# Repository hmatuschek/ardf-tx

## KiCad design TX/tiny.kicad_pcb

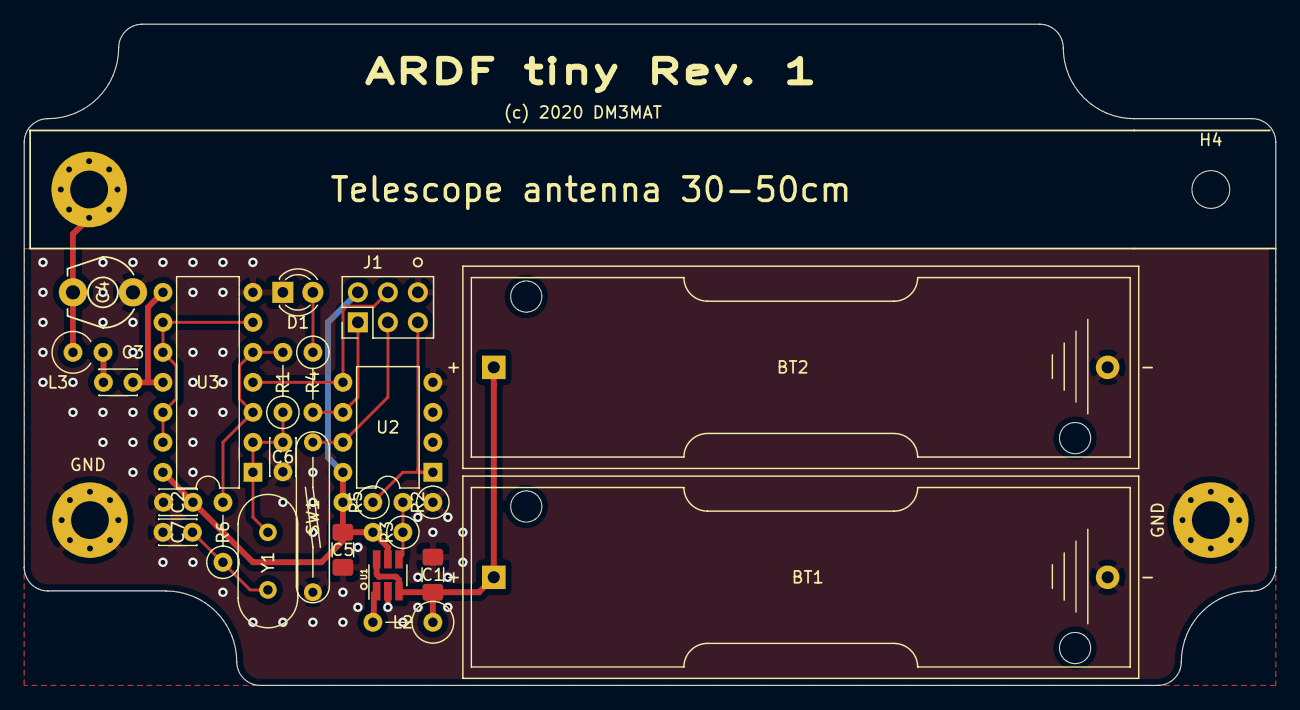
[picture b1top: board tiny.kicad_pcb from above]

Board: 2 copper layers, 106.0 x 56.0 mm, 28 parts (0 on the bottom side), 17 nets.

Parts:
BT1, BT2: 1.2V; BatteryHolder_Keystone_2460_1xAA
C1: 4.7u; C_1206_3216Metric_Pad1.42x1.75mm_HandSolder
C2, C3: 100n; C_Disc_D3.0mm_W2.0mm_P2.50mm
C4: 10p; C_Trimmer_TSC6_P5.00mm
C5: 10u; C_1206_3216Metric_Pad1.42x1.75mm_HandSolder
C6, C7: 33p; C_Disc_D3.0mm_W2.0mm_P2.50mm
D1: LED; LED_D3.0mm
H1: ANT; MountingHole_3.2mm_M3_Pad_Via
H2, H3: GND; MountingHole_3.2mm_M3_Pad_Via
H4: MountingHole; MountingHole_3.2mm_M3
J1: AVR-ISP-6; PinHeader_2x03_P2.54mm_Vertical
L2: 4.7u; L_Axial_L7.0mm_D3.3mm_P5.08mm_Vertical_Fastron_MICC
L3: 100u; L_Axial_L7.0mm_D3.3mm_P2.54mm_Vertical_Fastron_MICC
R1: 2.2M; R_Axial_DIN0207_L6.3mm_D2.5mm_P5.08mm_Vertical
R2: 562k; R_Axial_DIN0207_L6.3mm_D2.5mm_P2.54mm_Vertical
R3: 967k; R_Axial_DIN0207_L6.3mm_D2.5mm_P2.54mm_Vertical
R4: 650; R_Axial_DIN0207_L6.3mm_D2.5mm_P5.08mm_Vertical
R5: 10k; R_Axial_DIN0207_L6.3mm_D2.5mm_P2.54mm_Vertical
R6: 1.5k; R_Axial_DIN0207_L6.3mm_D2.5mm_P5.08mm_Vertical
SW1: Start/Stop; SW_Reed_Meder_MK6-5_P12.7
U1: MCP1640BCH; SOT-23-6_Handsoldering
U2: ATtiny45-20PU; DIP-8_W7.62mm
U3: 74HC00; DIP-14_W7.62mm
Y1: 3.579545; Crystal_HC49-U_Vertical

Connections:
+3V3: C2.2, C5.2, J1.2, R3.2, R5.2, U1.5, U2.8, U3.14
BTN: J1.3, SW1.1, U2.7
GND: BT1.2, BT2.2, C1.1, C2.1, C4.2, C5.1, C6.1, C7.1, D1.1, H2.1, H3.1, J1.6, R2.1, SW1.2, U1.2, U2.4, U3.7
KEY: J1.4, U2.5, U3.4
LED: J1.1, R4.2, U2.6
unnamed: BT1.1, BT2.1, C1.2, L2.1, U1.3, U1.6
unnamed: C3.1, U3.8, U3.11
unnamed: C3.2, L3.2
unnamed: C4.1, H1.1, L3.1
unnamed: C6.2, R1.1, U3.1, U3.2, Y1.1
unnamed: C7.2, R6.1, Y1.2
unnamed: D1.2, R4.1
unnamed: L2.2, U1.1
unnamed: R1.2, R6.2, U3.3, U3.5
unnamed: R2.2, R3.1, U1.4
unnamed: U3.6, U3.9, U3.10, U3.12, U3.13
RST: J1.5, R5.1, U2.1

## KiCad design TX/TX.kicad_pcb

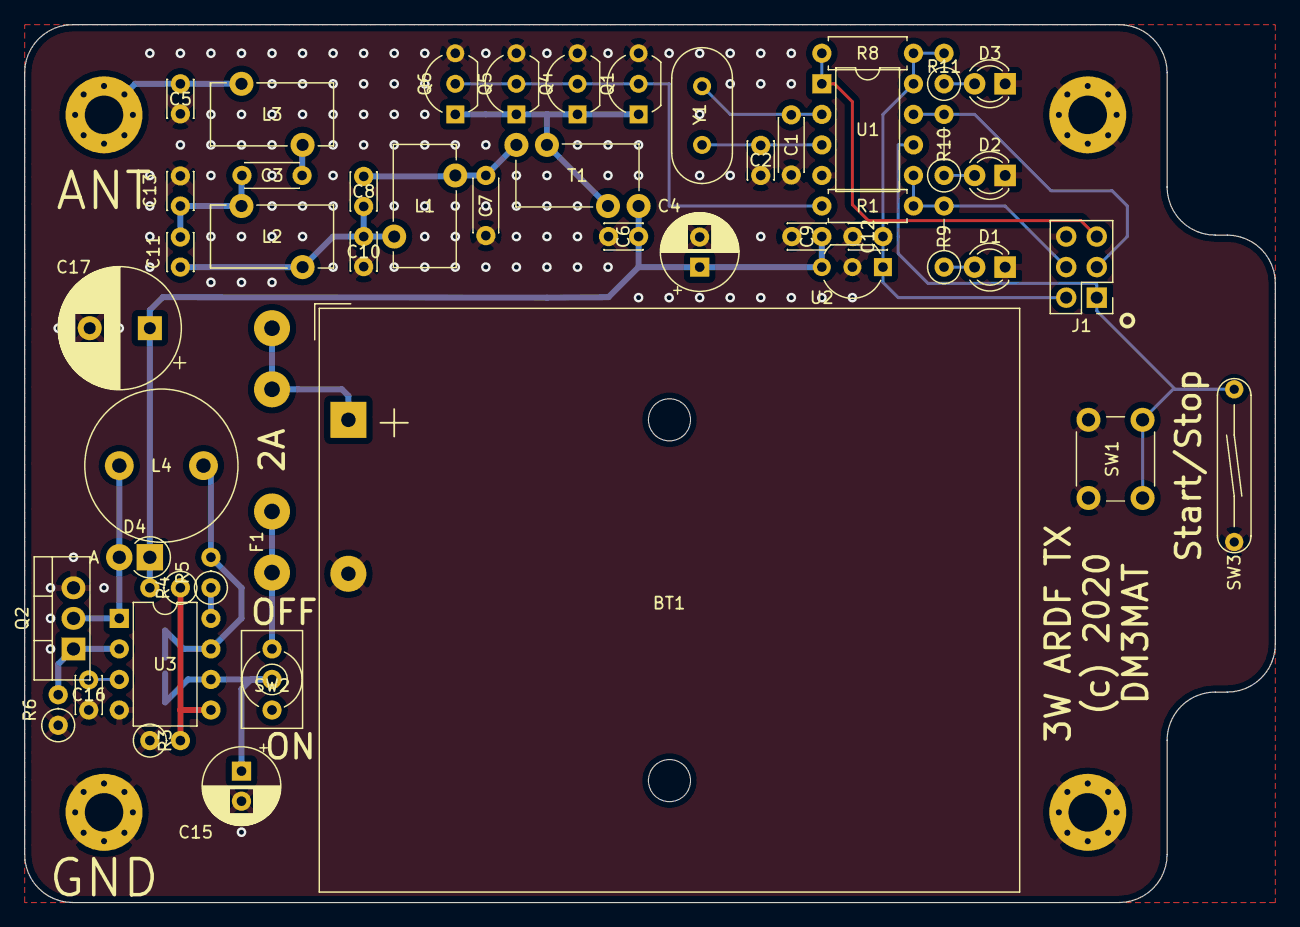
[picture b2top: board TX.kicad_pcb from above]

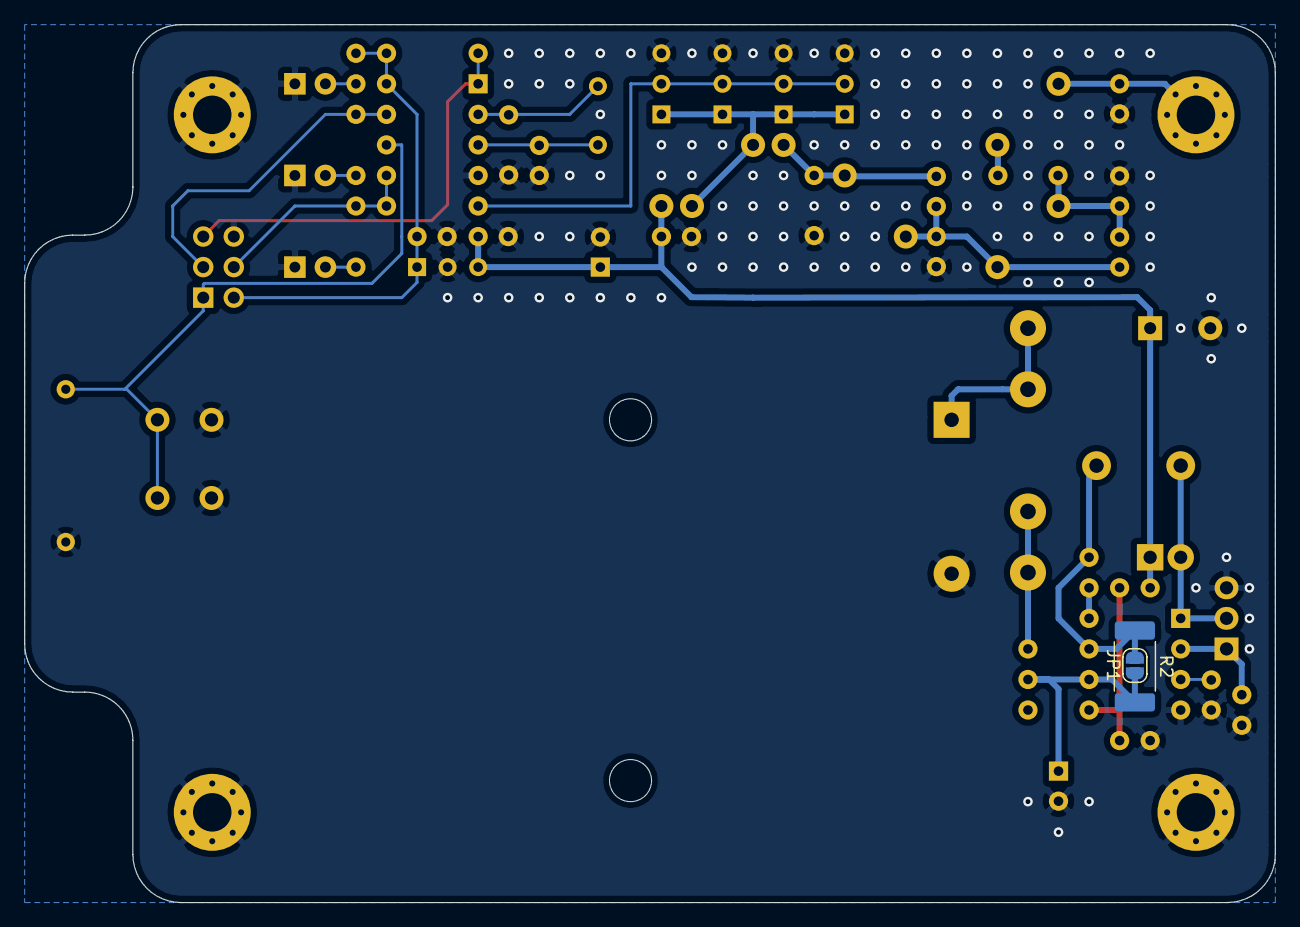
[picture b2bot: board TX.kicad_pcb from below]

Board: 2 copper layers, 104.0 x 73.0 mm, 55 parts (2 on the bottom side), 28 nets.

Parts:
BT1: 3.6V; BatteryHolder_TruPower_BH-331P_3xAA
C1: 22p; C_Disc_D4.3mm_W1.9mm_P5.00mm
C2: 22p; C_Disc_D3.0mm_W2.0mm_P2.50mm
C3: 220n; C_Disc_D4.3mm_W1.9mm_P5.00mm
C4: 100u; CP_Radial_D6.3mm_P2.50mm
C5: 47p; C_Disc_D3.0mm_W2.0mm_P2.50mm
C6, C9, C12: 100n; C_Disc_D3.0mm_W2.0mm_P2.50mm
C7: 820p; C_Disc_D4.3mm_W1.9mm_P5.00mm
C8: 150p; C_Disc_D3.0mm_W2.0mm_P2.50mm
C10: 1.2n; C_Disc_D3.0mm_W2.0mm_P2.50mm
C11: 390p; C_Disc_D3.0mm_W2.0mm_P2.50mm
C13: 560p; C_Disc_D3.0mm_W2.0mm_P2.50mm
C15: 220u; CP_Radial_D6.3mm_P2.50mm
C16: 470p; C_Disc_D3.0mm_W2.0mm_P2.50mm
C17: 470u; CP_Radial_D10.0mm_P5.00mm
D1, D2, D3: LED; LED_D3.0mm
D4: 1N5819; D_DO-41_SOD81_P2.54mm_Vertical_AnodeUp
F1: 2A Träge; Fuseholder_Cylinder-5x20mm_ESKA_Clip_Horizontal_Open
H1, H2, H3: GND; MountingHole_3.2mm_M3_Pad_Via
H4: ANT; MountingHole_3.2mm_M3_Pad_Via
J1: AVR-ISP-6; PinHeader_2x03_P2.54mm_Vertical
JP1: SolderJumper_2_Open; SolderJumper-2_P1.3mm_Open_RoundedPad1.0x1.5mm
L1: 2.2u; L_Toroid_Vertical_L10.0mm_W5.0mm_P5.08mm_Diagonal
L2: 1.8u; L_Toroid_Vertical_L10.0mm_W5.0mm_P5.08mm_Diagonal
L3: 42u; L_Toroid_Vertical_L10.0mm_W5.0mm_P5.08mm_Diagonal
L4: 20uH; L_Radial_D12.5mm_P7.00mm_Fastron_09HCP
Q1, Q4, Q5, Q6: BS170; TO-92_Inline_Wide
Q2: TIP41; TO-220-3_Vertical
R1: 100; R_Axial_DIN0207_L6.3mm_D2.5mm_P7.62mm_Horizontal
R2: 0.2; R_2512_6332Metric_Pad1.52x3.35mm_HandSolder
R3: 1k; R_Axial_DIN0207_L6.3mm_D2.5mm_P2.54mm_Vertical
R4: 6.2k; R_Axial_DIN0207_L6.3mm_D2.5mm_P2.54mm_Vertical
R5: 180; R_Axial_DIN0207_L6.3mm_D2.5mm_P2.54mm_Vertical
R6: 22; R_Axial_DIN0207_L6.3mm_D2.5mm_P2.54mm_Vertical
R8: 10k; R_Axial_DIN0207_L6.3mm_D2.5mm_P7.62mm_Horizontal
R9, R10: 1.5k; R_Axial_DIN0207_L6.3mm_D2.5mm_P5.08mm_Vertical
R11: 1.5k; R_Axial_DIN0207_L6.3mm_D2.5mm_P2.54mm_Vertical
SW1: Start/Stop; SW_PUSH_6mm_H7.3mm
SW2: ON; SW_Lever_RND-210-004371
SW3: EXT; SW_Reed_Meder_MK6-5_P12.7
T1: 2 x 10 @ FT37-43; Transformer_1P_1S_Toroid_Vertical_D10.5mm_Amidon-T37
U1: ATtiny45-20PU; DIP-8_W7.62mm
U2: L78L05; TO-92_Inline_Wide
U3: MC34063AP; DIP-8_W7.62mm
Y1: 14.31818MHz; Crystal_HC49-U_Vertical

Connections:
+5V: C12.1, J1.2, R8.2, R11.2, U1.8, U2.1
GND: BT1.2, C1.2, C2.2, C4.2, C5.2, C6.1, C7.2, C9.1, C10.2, C12.2, C13.2, C15.2, C16.2, C17.2, D1.1, D2.1, D3.1, H1.1, H2.1, H3.1, J1.6, Q1.3, Q2.3, Q4.3, Q5.3, Q6.3, R3.1, R6.1, SW1.2, SW3.2, U1.4, U2.2, U3.4
KEY: J1.4, R1.2, R9.2, U1.5
LED: J1.3, R10.2, U1.7
unnamed: BT1.1, F1.2
unnamed: C3.2, L3.1
unnamed: C5.1, H4.1, L3.2
unnamed: C7.1, C8.1, L1.1, T1.3
unnamed: C8.2, C10.1, C11.1, L1.2, L2.1
unnamed: C3.1, C11.2, C13.1, L2.2
unnamed: C15.1, JP1.1, R2.2, SW2.2, U3.6
unnamed: C16.1, U3.3
unnamed: D1.2, R9.1
unnamed: D2.2, R10.1
unnamed: D3.2, R11.1
unnamed: D4.2, L4.2, Q2.2, U3.1
unnamed: F1.1, SW2.1
unnamed: JP1.2, L4.1, R2.1, R5.2, U3.7
unnamed: Q1.1, Q4.1, Q5.1, Q6.1, T1.2, T1.4
unnamed: Q1.2, Q4.2, Q5.2, Q6.2, R1.1
unnamed: Q2.1, R6.2, U3.2
unnamed: R3.2, R4.1, U3.5
unnamed: R5.1, U3.8
RST: J1.5, R8.1, U1.1
SS: J1.1, SW1.1, SW3.1, U1.6
VCC: C4.1, C6.2, C9.2, C17.1, D4.1, R4.2, T1.1, U2.3
Xi: C1.1, U1.2, Y1.1
Xo: C2.1, U1.3, Y1.2

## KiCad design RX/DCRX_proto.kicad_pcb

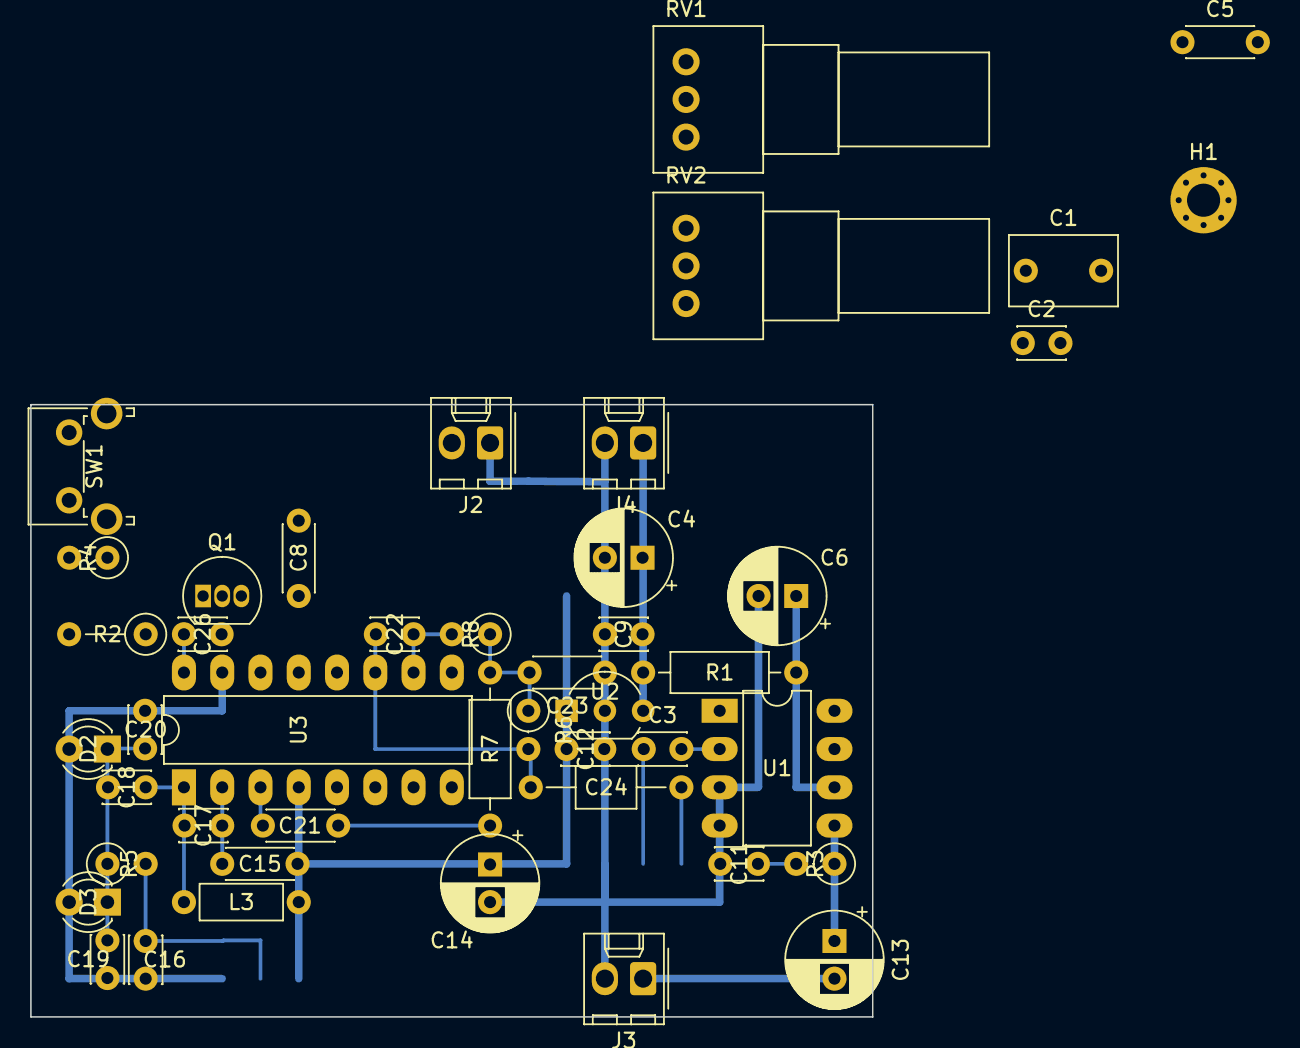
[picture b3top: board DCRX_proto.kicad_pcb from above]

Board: 2 copper layers, 55.9 x 40.6 mm, 45 parts (0 on the bottom side), 24 nets.

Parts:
C1: 30p; C_Rect_L7.0mm_W4.5mm_P5.00mm
C2: 220p; C_Disc_D3.0mm_W2.0mm_P2.50mm
C3, C9, C11, C12, C16, C18: 100n; C_Disc_D3.0mm_W2.0mm_P2.50mm
C4, C13: 100u; CP_Radial_D6.3mm_P2.50mm
C5, C8, C21: 100n; C_Disc_D4.3mm_W1.9mm_P5.00mm
C6, C14: 10u; CP_Radial_D6.3mm_P2.50mm
C15: 100p; C_Disc_D4.3mm_W1.9mm_P5.00mm
C17, C19: 100p; C_Disc_D3.0mm_W2.0mm_P2.50mm
C20: *; C_Disc_D3.0mm_W2.0mm_P2.50mm
C22: 2.2n; C_Disc_D3.0mm_W2.0mm_P2.50mm
C23: 47n; C_Disc_D4.3mm_W1.9mm_P5.00mm
C24: 100n; C_Axial_L3.8mm_D2.6mm_P10.00mm_Horizontal
C26: 1n; C_Disc_D3.0mm_W2.0mm_P2.50mm
D2, D3: LED; LED_D3.0mm
H1: EL; MountingHole_2.2mm_M2_Pad_Via
J2: MAG; Molex_KK-254_AE-6410-02A_1x02_P2.54mm_Vertical
J3: HP; Molex_KK-254_AE-6410-02A_1x02_P2.54mm_Vertical
J4: 9V; Molex_KK-254_AE-6410-02A_1x02_P2.54mm_Vertical
L3: 10u; L_Axial_L5.3mm_D2.2mm_P7.62mm_Horizontal_Vishay_IM-1
Q1: BF256C; TO-92_Inline
R1: 220; R_Axial_DIN0207_L6.3mm_D2.5mm_P10.16mm_Horizontal
R2: 1M; R_Axial_DIN0207_L6.3mm_D2.5mm_P5.08mm_Vertical
R3: 220; R_Axial_DIN0207_L6.3mm_D2.5mm_P2.54mm_Vertical
R4: 1k; R_Axial_DIN0207_L6.3mm_D2.5mm_P2.54mm_Vertical
R5: 100k; R_Axial_DIN0207_L6.3mm_D2.5mm_P2.54mm_Vertical
R6: 8.2k; R_Axial_DIN0207_L6.3mm_D2.5mm_P2.54mm_Vertical
R7: 820; R_Axial_DIN0207_L6.3mm_D2.5mm_P10.16mm_Horizontal
R8: 4.3k; R_Axial_DIN0207_L6.3mm_D2.5mm_P2.54mm_Vertical
RV1, RV2: 10k; Potentiometer_Alps_RK097_Single_Horizontal
SW1: SW_Push; SW_Tactile_SPST_Angled_PTS645Vx83-2LFS
U1: LM386; DIP-8_W7.62mm_LongPads
U2: L78L06; TO-92_Inline_Wide
U3: MC3361; DIP-16_W7.62mm_LongPads

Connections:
+6V: C8.2, C12.1, C14.1, C15.2, L3.2, Q1.3, RV1.1, U2.1, U3.4
AF: C3.1, RV2.2
GND: C1.2, C2.2, C4.2, C6.2, C8.1, C9.1, C11.1, C12.2, C14.2, C16.2, C19.2, C20.2, C23.1, D2.2, D3.2, J2.1, J3.2, J4.2, R2.2, R4.2, RV1.3, RV2.3, U1.3, U1.4, U2.2, U3.15
unnamed: C1.1, C2.1, C5.2, J2.2
unnamed: C3.2, U1.2
unnamed: C5.1, Q1.1, R2.1, SW1.2
unnamed: C6.1, R1.1, U1.6
unnamed: C11.2, R3.2
unnamed: C13.1, R3.1, U1.5
unnamed: C13.2, J3.1
unnamed: C15.1, C17.2, U3.2
unnamed: C16.1, R5.2, RV1.2
unnamed: C17.1, C18.1, L3.1, U3.1
unnamed: C18.2, C19.1, C20.1, D2.1, D3.1, R5.1
unnamed: C21.1, U3.3
unnamed: C21.2, R7.2
unnamed: C22.1, R8.2, U3.10
unnamed: C22.2, C24.2, R6.2, U3.11
unnamed: C23.2, R6.1, R7.1, R8.1
unnamed: C24.1, RV2.1
unnamed: C26.2, Q1.2, R4.1
unnamed: H1.1, SW1.1
PREAMP: C26.1, U3.16
VCC: C4.1, C9.2, J4.1, R1.2, U2.3

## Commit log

2020-01-27 Init.
2020-07-31 Tiny release.
2020-07-31 Cleanup.
2025-08-05 Fixed build script.

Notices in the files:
TX/TX.kicad_pcb:
(c) 2020
TX/tiny.kicad_pcb:
(c) 2020 DM3MAT
